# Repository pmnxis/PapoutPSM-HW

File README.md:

# PapoutPSM-HW

| 3D Model | Real Image |
| -------- | ---------- |
|  |  |

Parallel to Serial Adapter for Korean Paper Dispenser Machine.
Some wellknown korean paper dispenser have two type of device.
Serial model communicate to host with RS232.

## PCB Specification
- DRC/Fabrication Clearance : JLCPCB Standard 2 Layer Spec.
- PCB : 2Layer FR4 ; 1.6T , Considerd on black colour.
- Size : 80mm * 50mm

## Power Connection
### 12V Usage (Normal)
- Connect Secondary Power Source (ACDC Adapter) 12VDC (5A) to barral jack.
- Use default varistor (RV1). Default is `10Ø 18V`.

### 24V Usage
- Connect Secondary Power Source (ACDC Adapter) 24VDC (3A) to barral jack.
- Use custom varistor (RV1). Must be higher or eqeual with `30V`.

### Programming
- MSP430FR2433 with CCStudio.
- or with Rust? https://github.com/rust-embedded/msp430-quickstart
- Emulating dispenser machine should count exhaust or some configuration on non violent storage. MSP43FR have internal FeRAM. Thus ensure high durability on many write operation.

### Related Project 
https://github.com/pmnxis/papout-psm-rs

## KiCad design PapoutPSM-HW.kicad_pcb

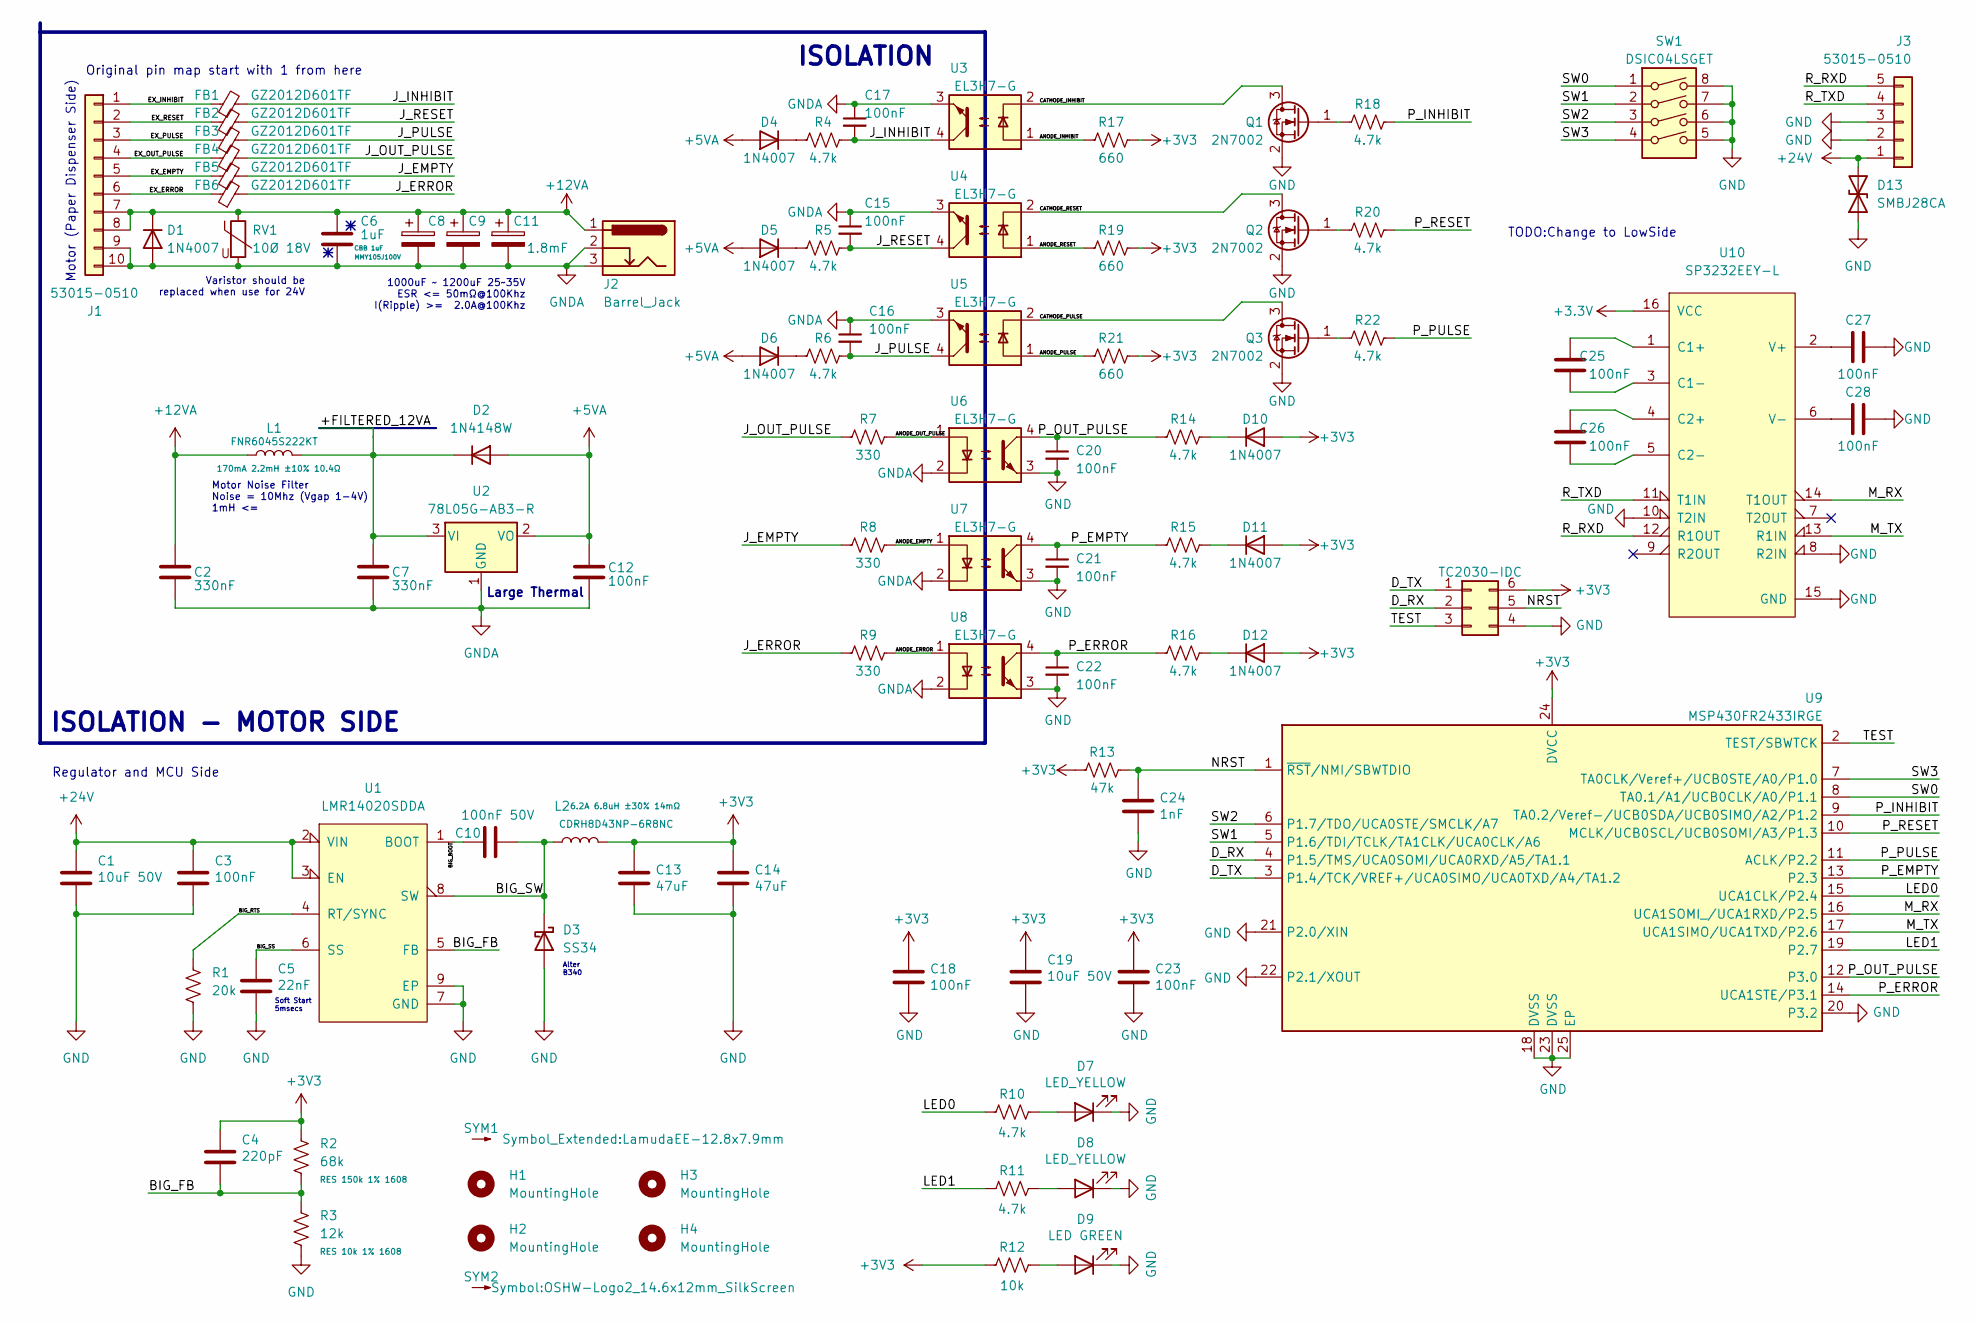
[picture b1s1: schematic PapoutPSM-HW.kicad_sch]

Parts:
C1, C19: 10uF 50V; C_0805_2012Metric; MFR.Part# GRM21BR61H106KE43L; LCSC Part C440198
C2, C7: 330nF; C_0805_2012Metric; MFR.Part# 0805B334K500NT; LCSC Part C1740
C3, C12, C15, C16, C17, C18, C20, C21, C22, C23, C25, C26, C27, C28: 100nF; C_0402_1005Metric; MFR.Part# CL05B104KB54PNC; LCSC Part C307331
C4: 220pF; C_0603_1608Metric; MFR.Part# CL10C331JB8NNNC; LCSC Part C1664
C5: 22nF; C_0603_1608Metric; MFR.Part# CL10B223KB8NNNC; LCSC Part C21122
C6: 1uF; C_Rect_L7.5mm_W6.5mm_P5.00mm; MFR.Part# MMY105J100V
C8, C9, C11: 1.8mF; CP_Radial_D12.5mm_P5.00mm; MFR.Part# LKML2501V182MF; LCSC Part C442894
C10: 100nF 50V; C_0603_1608Metric; MFR.Part# CC0603KRX7R9BB104; LCSC Part C14663
C13, C14: 47uF; C_1210_3225Metric; MFR.Part# GRM32ER61C476KE15L; LCSC Part C77101
C24: 1nF; C_0402_1005Metric; MFR.Part# 0402B102K500NT; LCSC Part C1523
D1: 1N4007; D_DO-41_SOD81_P10.16mm_Horizontal
D2: 1N4148W; D_SOD-123
D3: SS34; D_SMA; MFR.Part# SS34; LCSC Part C8678
D4, D5, D6, D10, D11, D12: 1N4007; D_SOD-123F
D7, D8: LED_YELLOW; LED_0805_2012Metric; MFR.Part# KT-0805Y; LCSC Part C2296
D9: LED GREEN; LED_0805_2012Metric; MFR.Part# KT-0805G; LCSC Part C2297
D13: SMBJ28CA; D_SMB; MFR.Part# SMBJ28CA; LCSC Part C151259
DEBUG1: TC2030-IDC; Tag-Connect_TC2030-IDC-FP_2x03_P1.27mm_Vertical
FB1, FB2, FB3, FB4, FB5, FB6: GZ2012D601TF; L_0805_2012Metric; MFR.Part# GZ2012D601TF; LCSC Part C1017
H1, H2, H3, H4: MountingHole; MountingHole_4.3mm_M4_ISO14580_Pad
J1: 53015-0510; Molex_MicroBlade_53015-1000_1x10_P2.00mm_Right; MFR.Part# 53015-1010
J2: Barrel_Jack; BarrelJack_GCT_DCJ200-10-A_Horizontal
J3: 53015-0510; Molex_MicroBlade_53015-0500_1x05_P2.00mm_Right; MFR.Part# 53015-0510
L1: FNR6045S222KT; L_Bourns_SRN6045TA; MFR.Part# FNR6045S222KT; LCSC Part C168104
L2: CDRH8D43NP-6R8NC; L_Bourns-SRU8028_8.0x8.0mm; MFR.Part# CDRH8D43NP-6R8NC; LCSC Part C225026
Q1, Q2, Q3: 2N7002; SOT-23
R1: 20k; R_0603_1608Metric; MFR.Part# 0603WAF2002T5E; LCSC Part C4184
R2: 68k; R_0603_1608Metric; MFR.Part# 0603WAF1503T5E; LCSC Part C22807
R3: 12k; R_0603_1608Metric; MFR.Part# 0603WAF1002T5E; LCSC Part C25804
R4, R5, R6, R10, R11, R14, R15, R16, R18, R20, R22: 4.7k; R_0402_1005Metric; MFR.Part# 0402WGF4701TCE; LCSC Part C25900
R7, R8, R9: 330; R_0603_1608Metric
R12: 10k; R_0402_1005Metric; MFR.Part# 0402WGF1002TCE; LCSC Part C25744
R13: 47k; R_0402_1005Metric; MFR.Part# 0402WGF4702TCE; LCSC Part C25792
R17, R19, R21: 660; R_0603_1608Metric
RV1: 10Ø 18V; RV_Disc_D12mm_W4.3mm_P7.5mm
SW1: DSIC04LSGET; SW_DIP_SPSTx04_Slide_9.30x10.16mm_W4.25mm_P2.54mm
SYM1: SYM_Arrow_Tiny; LamudaEE-12.8x7.9mm
SYM2: SYM_Arrow_Tiny; OSHW-Logo2_14.6x12mm_SilkScreen
U1: LMR14020SDDA; TI_SO-PowerPAD-8_ThermalVias; MFR.Part# LMR14050SDDAR; LCSC Part C155484
U2: 78L05G-AB3-R; SOT-89-3; MFR.Part# 78L05G-AB3-R; LCSC Part C71136
U3, U4, U5, U6, U7, U8: EL3H7-G; SMDIP-4_W5.20mm; MFR.Part# EL3H7(B)(TA)-G; LCSC Part C32565
U9: MSP430FR2433IRGE; HVQFN-24-1EP_4x4mm_P0.5mm_EP2.5x2.5mm; MFR.Part# MSP430FR2433IRGER; LCSC Part C191026
U10: SP3232EEY-L; TSSOP-16_4.4x5mm_P0.65mm; MFR.Part# SP3232EEY-L; LCSC Part C13482

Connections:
+5VA: C12.1, D2.2 (A), D4.2 (A), D5.2 (A), D6.2 (A), U2.2 (VO)
+12VA: C2.1, C6.1, C8.1, C9.1, C11.1, D1.1 (K), J1.7, J1.8, J2.1, L1.1, RV1.1
+24V: C1.1, C3.1, D13.2 (A2), J3.1, U1.2 (VIN), U1.3 (EN)
/+FILTERED_12VA: C7.1, D2.1 (K), L1.2, U2.3 (VI)
/ANODE_EMPTY: R8.2, U7.1
/ANODE_ERROR: R9.2, U8.1
/ANODE_INHIBIT: R17.1, U3.1
/ANODE_OUT_PULSE: R7.2, U6.1
/ANODE_PULSE: R21.1, U5.1
/ANODE_RESET: R19.1, U4.1
/BIG_BOOT: C10.1, U1.1 (BOOT)
/BIG_FB: C4.2, R2.2, R3.1, U1.5 (FB)
/BIG_RTS: R1.1, U1.4 (RT/SYNC)
/BIG_SS: C5.1, U1.6 (SS)
/BIG_SW: C10.2, D3.1 (K), L2.1, U1.8 (SW)
/CATHODE_INHIBIT: Q1.3 (D), U3.2
/CATHODE_PULSE: Q3.3 (D), U5.2
/CATHODE_RESET: Q2.3 (D), U4.2
/D_RX: DEBUG1.2, U9.4 (P1.5/TMS/UCA0SOMI/UCA0RXD/A5/TA1.1)
/D_TX: DEBUG1.1, U9.3 (P1.4/TCK/VREF+/UCA0SIMO/UCA0TXD/A4/TA1.2)
/EX_EMPTY: FB5.1, J1.5
/EX_ERROR: FB6.1, J1.6
/EX_INHIBIT: FB1.1, J1.1
/EX_OUT_PULSE: FB4.1, J1.4
/EX_PULSE: FB3.1, J1.3
/EX_RESET: FB2.1, J1.2
/J_EMPTY: FB5.2, R8.1
/J_ERROR: FB6.2, R9.1
/J_INHIBIT: C17.2, FB1.2, R4.2, U3.4
/J_OUT_PULSE: FB4.2, R7.1
/J_PULSE: C16.2, FB3.2, R6.2, U5.4
/J_RESET: C15.2, FB2.2, R5.2, U4.4
/LED0: R10.1, U9.15 (UCA1CLK/P2.4)
/LED1: R11.1, U9.19 (P2.7)
/M_RX: U9.16 (UCA1SOMI_/UCA1RXD/P2.5), U10.14 (T1OUT)
/M_TX: U9.17 (UCA1SIMO/UCA1TXD/P2.6), U10.13 (R1IN)
/NRST: C24.1, DEBUG1.5, R13.1, U9.1 (~RST/NMI/SBWTDIO)
/P_EMPTY: C21.1, R15.2, U7.4, U9.13 (P2.3)
/P_ERROR: C22.1, R16.2, U8.4, U9.14 (UCA1STE/P3.1)
/P_INHIBIT: R18.2, U9.9 (TA0.2/Veref-/UCB0SDA/UCB0SIMO/A2/P1.2)
/P_OUT_PULSE: C20.1, R14.2, U6.4, U9.12 (P3.0)
/P_PULSE: R22.2, U9.11 (ACLK/P2.2)
/P_RESET: R20.2, U9.10 (MCLK/UCB0SCL/UCB0SOMI/A3/P1.3)
/R_RXD: J3.5, U10.12 (R1OUT)
/R_TXD: J3.4, U10.11 (T1IN)
/SW0: SW1.1, U9.8 (TA0.1/A1/UCB0CLK/A0/P1.1)
/SW1: SW1.2, U9.5 (P1.6/TDI/TCLK/TA1CLK/UCA0CLK/A6)
/SW2: SW1.3, U9.6 (P1.7/TDO/UCA0STE/SMCLK/A7)
/SW3: SW1.4, U9.7 (TA0CLK/Veref+/UCB0STE/A0/P1.0)
/TEST: DEBUG1.3, U9.2 (TEST/SBWTCK)
GND: C1.2, C3.2, C5.2, C13.2, C14.2, C18.2, C19.2, C20.2, C21.2, C22.2, C23.2, C24.2, C27.1, C28.1, D3.2 (A), D7.1 (K), D8.1 (K), D9.1 (K), D13.1 (A1), DEBUG1.4, J3.2, J3.3, Q1.2 (S), Q2.2 (S), Q3.2 (S), R1.2, R3.2, SW1.5, SW1.6, SW1.7, SW1.8, U1.7 (GND), U1.9 (EP), U6.3, U7.3, U8.3, U9.18 (DVSS), U9.20 (P3.2), U9.21 (P2.0/XIN), U9.22 (P2.1/XOUT), U9.23 (DVSS), U9.25 (EP), U10.8 (R2IN), U10.10 (T2IN), U10.15 (GND)
GNDA: C2.2, C6.2, C7.2, C8.2, C9.2, C11.2, C12.2, C15.1, C16.1, C17.1, D1.2 (A), J1.9, J1.10, J2.2, J2.3, RV1.2, U2.1 (GND), U3.3, U4.3, U5.3, U6.2, U7.2, U8.2
unnamed: C25.1, U10.3 (C1-)
unnamed: C25.2, U10.1 (C1+)
unnamed: C26.1, U10.5 (C2-)
unnamed: C26.2, U10.4 (C2+)
unnamed: C27.2, U10.2 (V+)
unnamed: C28.2, U10.6 (V-)
unnamed: D4.1 (K), R4.1
unnamed: D5.1 (K), R5.1
unnamed: D6.1 (K), R6.1
unnamed: D7.2 (A), R10.2
unnamed: D8.2 (A), R11.2
unnamed: D9.2 (A), R12.2
unnamed: D10.1 (K), R14.1
unnamed: D11.1 (K), R15.1
unnamed: D12.1 (K), R16.1
unnamed: Q1.1 (G), R18.1
unnamed: Q2.1 (G), R20.1
unnamed: Q3.1 (G), R22.1

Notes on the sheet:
Alter B340
Soft Start 5msecs
Regulator and MCU Side
1000uF ~ 1200uF 25~35V ESR <= 50mΩ@100Khz I(Ripple) >= 2.0A@100Khz
ISOLATION
TODO:Change to LowSide
Motor Noise Filter Noise = 10Mhz (Vgap 1-4V) 1mH <=
Large Thermal
ISOLATION - MOTOR SIDE
Original pin map start with 1 from here
Varistor should be replaced when use for 24V
Motor (Paper Dispenser Side)

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
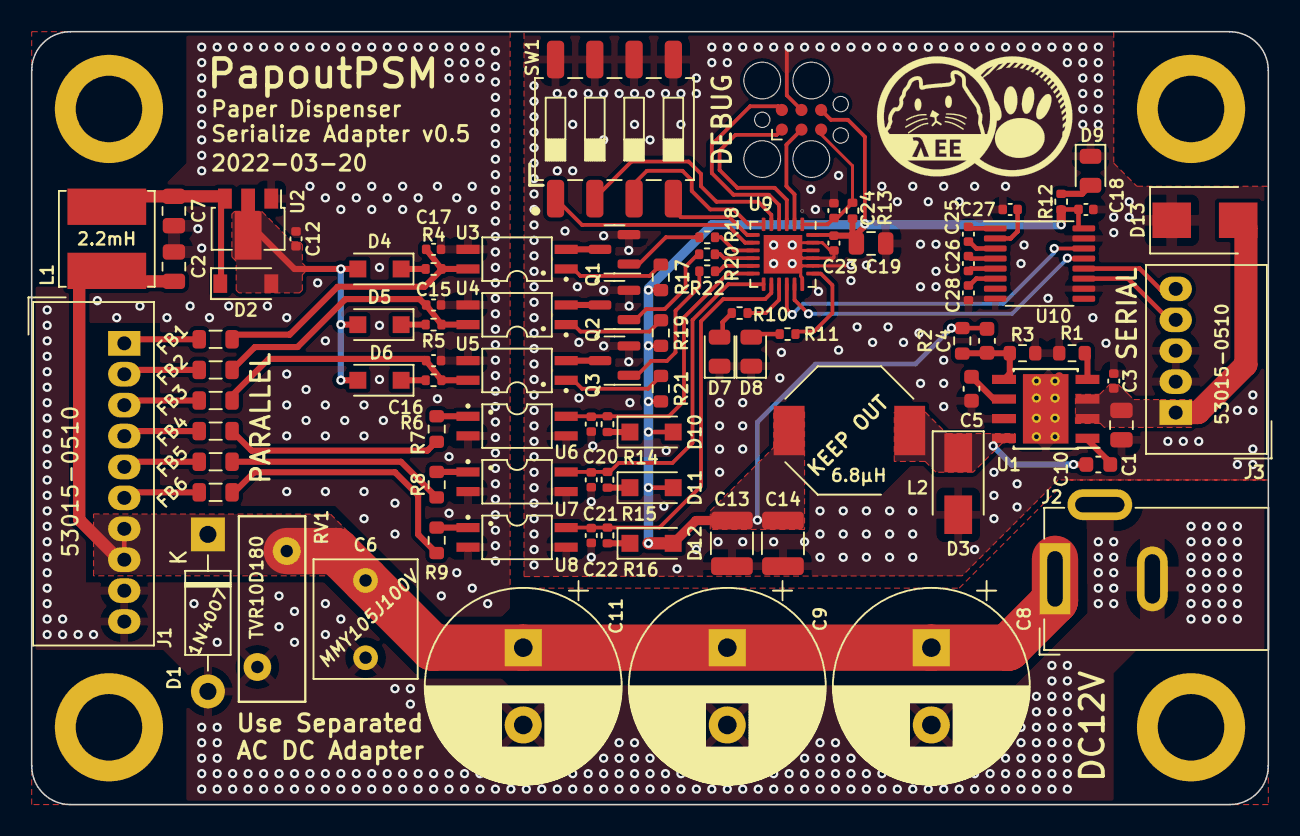
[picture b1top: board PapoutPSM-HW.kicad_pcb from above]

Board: 2 copper layers, 80.0 x 50.0 mm, 96 parts (1 on the bottom side), 71 nets.

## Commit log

2021-07-27 init
2021-07-28 stuff
2021-07-28 update bom
2021-07-28 Update fp-info-cache
2021-07-28 update bom2
2021-07-29 updates pdf.
2021-07-31 pre 2
2021-10-09 Initial with v4 state
2021-10-09 clean up some
2021-10-10 some layout changed (sizeup for later 2layer conversion)
2022-01-31 released kicad 6.0
2022-03-20 release/v3 update
2022-03-20 before release v0.5
2022-03-20 Update gitignore
2022-04-03 Update latest changes on low-side NMos usage

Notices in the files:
PapoutPSM-HW.kicad_pcb:
CERN-OHL-S-2.0
